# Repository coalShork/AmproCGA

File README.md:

# AmproCGA
A CGA card for the Ampro Little Board PC. Takes CPLDs from a generic Chinese CGA card for compactness.

The CPLDs used in this are from [this card.](https://8086cpu.com/lm6/79.html) 
If you intend to build one you will need to purchase that card from eBay or something and transfer the ICs to my board.
As of writing this, the board has not been tested, do not expect it to work first try. I expect there will be some hiccups.

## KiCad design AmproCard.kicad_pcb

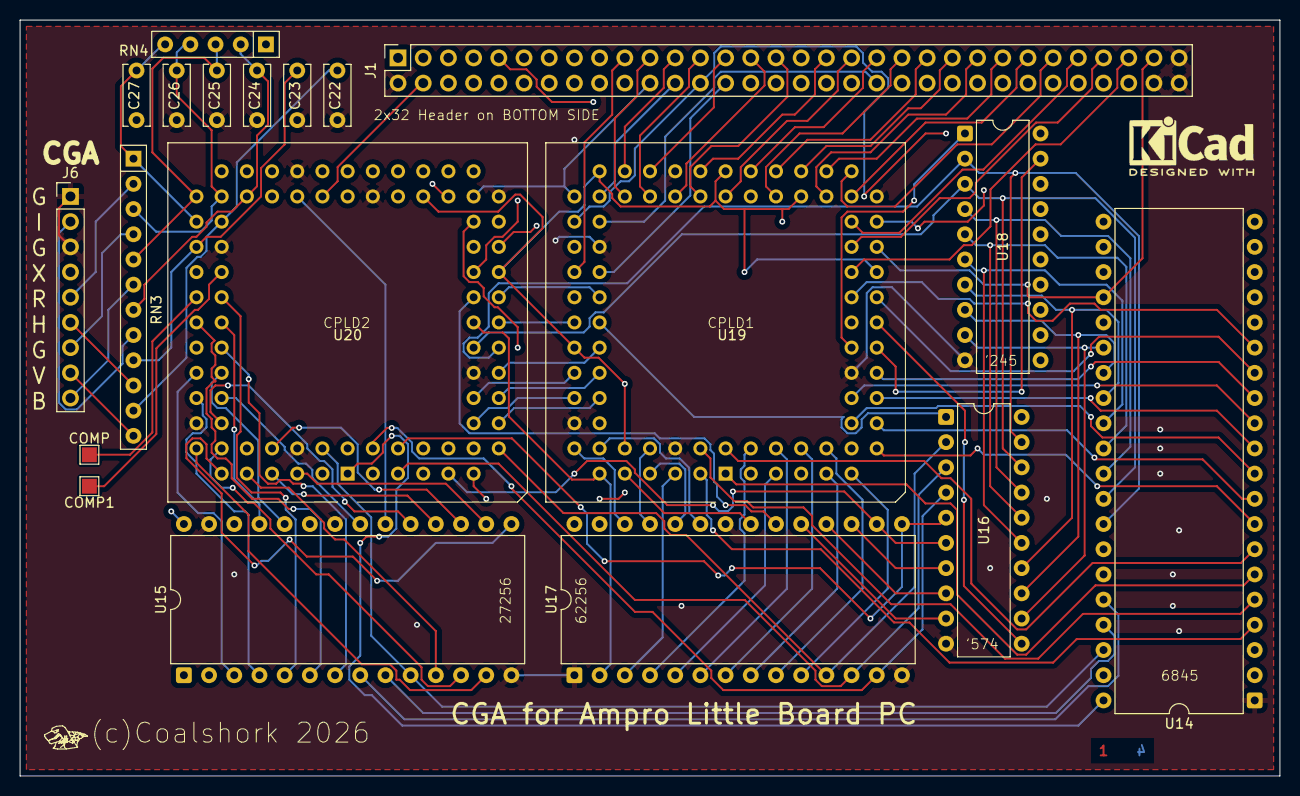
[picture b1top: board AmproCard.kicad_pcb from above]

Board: 4 copper layers, 127.0 x 76.2 mm, 20 parts (0 on the bottom side), 136 nets.

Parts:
C22, C23, C24, C25, C26, C27: 47pF; C_Disc_D6.0mm_W2.5mm_P5.00mm
COMP, COMP1: TestPoint_Pad_1.5x1.5mm
CoalLogo: Val**; CoalLogo
J1: Conn_02x32_Odd_Even; PinSocket_2x32_P2.54mm_Vertical
J6: CGA; PinHeader_1x09_P2.54mm_Vertical
RN3: 33; R_Array_SIP12
RN4: 4.7K; R_Array_SIP5
U14: MC6845; DIP-40_W15.24mm
U15: 27C256; DIP-28_W15.24mm
U16: 74LS574; DIP-20_W7.62mm
U17: KM62256CLP; DIP-28_W15.24mm
U18: 74HC245; DIP-20_W7.62mm
U19, U20: CGA CPLD 1; PLCC-84_THT-Socket

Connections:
6845-CS: U14.25 (~CS), U19.30 (6845CS)
6845-E: U14.23 (E), U19.23 (6845-E)
+5V: J1.6, J1.58, RN4.1 (common), U14.20 (VCC), U15.2 (A12), U15.23 (A11), U15.28 (VCC), U16.20 (VCC), U17.28 (VCC), U18.20 (VCC), U19.3 (VCC), U19.13 (VCC), U19.26 (VCC), U19.38 (VCC), U19.43 (VCC), U19.53 (VCC), U19.66 (VCC), U19.78 (VCC), U20.3 (VCC), U20.13 (VCC), U20.26 (VCC), U20.38 (VCC), U20.43 (VCC), U20.53 (VCC), U20.66 (VCC), U20.78 (VCC)
A0: J1.61, U14.24 (RS), U19.28 (A0)
A1: J1.59, U19.27 (A1)
A2: J1.57, U19.29 (A2)
A3: J1.55, U19.31 (A3)
A4: J1.53, U19.33 (A4)
A5: J1.51, U19.34 (A5)
A6: J1.49, U19.35 (A6)
A7: J1.47, U19.36 (A7)
A8: J1.45, U19.37 (A8)
A9: J1.43, U19.39 (A9)
A10: J1.41, U19.40 (A10)
A11: J1.39, U19.41 (A11)
A12: J1.37, U19.44 (A12)
A13: J1.35, U19.45 (A13)
A15: J1.31, U19.46 (A15)
A16: J1.29, U19.48 (A16)
A17: J1.27, U19.49 (A17)
A18: J1.25, U19.50 (A18)
A19: J1.23, U19.51 (A19)
AEN: J1.21, U19.52 (AEN)
BLUE: C25.1, RN3.5 (R3.1), RN4.3 (R2), U20.54 (B)
CA0: U14.4 (MA0), U19.83 (CRTMA0)
CA1: U14.5 (MA1), U19.84 (CRTMA1)
CA2: U14.6 (MA2), U19.1 (CRTMA2)
CA3: U14.7 (MA3), U19.2 (CRTMA3)
CA4: U14.8 (MA4), U19.12 (CRTMA4)
CA5: U14.9 (MA5), U19.14 (CRTMA5)
CA6: U14.10 (MA6), U19.15 (CRTMA6)
CA7: U14.11 (MA7), U19.16 (CRTMA7)
CA8: U14.12 (MA8), U19.17 (CRTMA8)
CA9: U14.13 (MA9), U19.18 (CRTMA9)
CA10: U14.14 (MA10), U19.24 (CRTMA10)
CA11: U14.15 (MA11), U19.25 (CRTMA11)
CA12: U14.16 (MA12), U20.37 (CRTMA12)
CBLUE: J6.9, RN3.6 (R3.2)
CC0: U15.7 (A3), U20.67 (CC0)
CC1: U15.6 (A4), U20.64 (CC1)
CC2: U15.5 (A5), U20.63 (CC2)
CC3: U15.4 (A6), U20.70 (CC3)
CC4: U15.3 (A7), U20.68 (CC4)
CC5: U15.25 (A8), U20.65 (CC5)
CC6: U15.24 (A9), U20.69 (CC6)
CC7: U15.21 (A10), U20.71 (CC7)
CCLK: U14.21 (CLK), U20.40 (CCLK)
CGREEN: J6.7, RN3.4 (R2.2)
CHSYNC: J6.6, RN3.10 (R5.2)
CINTENSITY: J6.2, RN3.8 (R4.2)
CLK: J1.40, U19.57 (IOCLK)
COMP: COMP.1, U20.62 (COMP-OUT)
COMP1: COMP1.1, U20.61 (COMP-OUT151)
CRED: J6.5, RN3.2 (R1.2)
CURSOR: U14.19 (CURSOR), U20.28 (CURSOR)
CVSYNC: J6.8, RN3.12 (R6.2)
D0: J1.17, U18.18 (B0)
D1: J1.15, U18.17 (B1)
D2: J1.13, U18.16 (B2)
D3: J1.11, U18.15 (B3)
D4: J1.9, U18.14 (B4)
D5: J1.7, U18.13 (B5)
D6: J1.5, U18.12 (B6)
D7: J1.3, U18.11 (B7)
DATA-DIR: U18.1 (A->B), U19.21 (DATADIR)
DATA-GATE: U18.19 (CE), U19.20 (DATAGATE)
DB0: U14.33 (D0), U16.19 (Q0), U18.2 (A0), U20.20 (DB0)
DB1: U14.32 (D1), U16.18 (Q1), U18.3 (A1), U20.21 (DB1)
DB2: U14.31 (D2), U16.17 (Q2), U18.4 (A2), U20.27 (DB2)
DB3: U14.30 (D3), U16.16 (Q3), U18.5 (A3), U20.29 (DB3)
DB4: U14.29 (D4), U16.15 (Q4), U18.6 (A4), U20.30 (DB4)
DB5: U14.28 (D5), U16.14 (Q5), U18.7 (A5), U20.35 (DB5)
DB6: U14.27 (D6), U16.13 (Q6), U18.8 (A6), U20.33 (DB6)
DB7: U14.26 (D7), U16.12 (Q7), U18.9 (A7), U20.36 (DB7)
DISPEN: U14.18 (DE), U20.31 (DISPEN)
DOT0: U15.11 (D0), U20.77 (DOT0)
DOT1: U15.12 (D1), U20.76 (DOT1)
DOT2: U15.13 (D2), U20.74 (DOT2)
DOT3: U15.15 (D3), U20.75 (DOT3)
DOT4: U15.16 (D4), U20.81 (DOT4)
DOT5: U15.17 (D5), U20.80 (DOT5)
DOT6: U15.18 (D6), U20.79 (DOT6)
DOT7: U15.19 (D7), U20.73 (DOT7)
ENCPUADDR: U19.67 (ENCPUADD), U20.18 (EN-CPU-ADDR)
GND: C22.2, C23.2, C24.2, C25.2, C26.2, C27.2, J1.2, J1.20, J1.62, J1.63, J1.64, J6.1, J6.3, U14.1 (GND), U15.14 (GND), U15.22 (~OE), U15.26 (A13), U15.27 (A14), U16.10 (GND), U17.1 (A14), U17.14 (GND), U17.22 (~OE), U18.10 (GND), U19.7 (GND), U19.19 (GND), U19.32 (GND), U19.42 (GND), U19.47 (GND), U19.59 (GND), U19.72 (GND), U19.82 (GND), U20.7 (GND), U20.19 (GND), U20.32 (GND), U20.42 (GND), U20.47 (GND), U20.59 (GND), U20.72 (GND), U20.82 (GND)
GREEN: C26.1, RN3.3 (R2.1), RN4.4 (R3), U20.55 (G)
HSYNC: U14.39 (HS), U20.2 (VSYNC)
HSYNC1: C23.1, RN3.9 (R5.1), U20.58 (HSYNC-O1)
INTENSITY: C24.1, RN3.7 (R4.1), RN4.2 (R1), U20.52
IOR: J1.28, U19.61 (IOR#)
IOW: J1.26, U14.22 (R/~W), U19.56 (IOW)
I/OCHRDY: J1.19, U19.60 (IOREADY)
MD0: U16.2 (D0), U17.11 (Q0), U20.12 (MD0)
MD1: U16.3 (D1), U17.12 (Q1), U20.5 (MD1)
MD2: U16.4 (D2), U17.13 (Q2), U20.4 (MD2)
MD3: U16.5 (D3), U17.15 (Q3), U20.6 (MD3)
MD4: U16.6 (D4), U17.16 (Q4), U20.9 (MD4)
MD5: U16.7 (D5), U17.17 (Q5), U20.11 (MD5)
MD6: U16.8 (D6), U17.18 (Q6), U20.8 (MD6)
MD7: U16.9 (D7), U17.19 (Q7), U20.10 (MD7)
MEMR: J1.24, U19.55 (MEMR)
MEMW: J1.22, U19.54 (MEMW), U20.34 (MEMW)
unnamed: U19.70 (MA12OUT), U20.15 (MA12OUT)
unnamed: U19.71 (Q1), U20.14 (O1)
unnamed: U19.68 (SEL1), U20.17 (SEL1)
unnamed: U19.69 (SEL2), U20.16 (SEL2)
unnamed: U19.63 (STATSEL), U20.24 (STATSEL)
OSC: J1.60, U20.39 (OSC)
RA0: U14.38 (RA0), U15.10 (A0), U20.84 (RA0)
RA1: U14.37 (RA1), U15.9 (A1)
RA2: U14.36 (RA2), U15.8 (A2)
RAMA0: U17.10 (A0), U19.11 (RAMA0)
RAMA1: U17.9 (A1), U19.10 (RAMA1)
RAMA2: U17.8 (A2), U19.9 (RAMA2)
RAMA3: U17.7 (A3), U19.8 (RAMA3)
RAMA4: U17.6 (A4), U19.6 (RAMA4)
RAMA5: U17.5 (A5), U19.5 (RAMA5)
RAMA6: U17.4 (A6), U19.4 (RAMA6)
RAMA7: U17.3 (A7), U19.81 (RAMA7)
RAMA8: U17.25 (A8), U19.80 (RAMA8)
RAMA9: U17.24 (A9), U19.79 (RAMA9)
RAMA10: U17.21 (A10), U19.77 (RAMA10)
RAMA11: U17.23 (A11), U19.76 (RAMA11)
RAMA12: U17.2 (A12), U19.75 (RAMA12), U20.23 (RAM-A12)
RAMA13: U17.26 (A13), U19.74 (RAMA13)
RCS: U17.20 (~CS), U20.25 (RAMCS)
RD-GATE: U16.1 (OE), U19.65 (RDGATE)
RED: C27.1, RN3.1 (R1.1), RN4.5 (R4), U20.56 (R)
RESET: J1.4, U20.46 (~RESET)
ROMCS: U15.20 (~CE), U20.48 (ROMCS)
RWE: U17.27 (~WE), U20.41 (WE)
U2-6: U19.64 (U2-6), U20.22 (U2-6)
VSYNC: U14.40 (VS), U20.1 (HSYNC)
VSYNC1: C22.1, RN3.11 (R6.1), U20.57 (VSYNC-O1)
XACK: U16.11 (Cp), U19.22 (XACK)
~RAS: U19.73 (RAS), U20.45 (RAS)
